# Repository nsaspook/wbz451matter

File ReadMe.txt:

Folder & File List:
Altium CAD\WBZ451 Curiosity Board-R7.zip: Contains the Altium Design Source Files for WBZ451 Curiosity Board
BOM\02-00307-R7_BOM.xls: Contains the Bill Of Materials for WBZ451 Curiosity Board
Gerber\05-00307-R4_PNP: Contains the pick and place files for WBZ451 Curiosity Board
Gerber\05-11423-R4: Contains the release gerber files for WBZ451 Curiosity Board
Gerber\04-11423-R4-D.pdf: Contains the Fab drawing for WBZ451 Curiosity Board
Gerber\04-11423-R4-PCB.pdf: Contains the PCB layer drawing for WBZ451 Curiosity Board
Gerber\05-00307-R4.pdf: Contains the Assembly drawings and 3D images for WBZ451 Curiosity Board
Schematics\03-00307-R7.pdf: Contains the Schematic drawing for WBZ451 Curiosity Board

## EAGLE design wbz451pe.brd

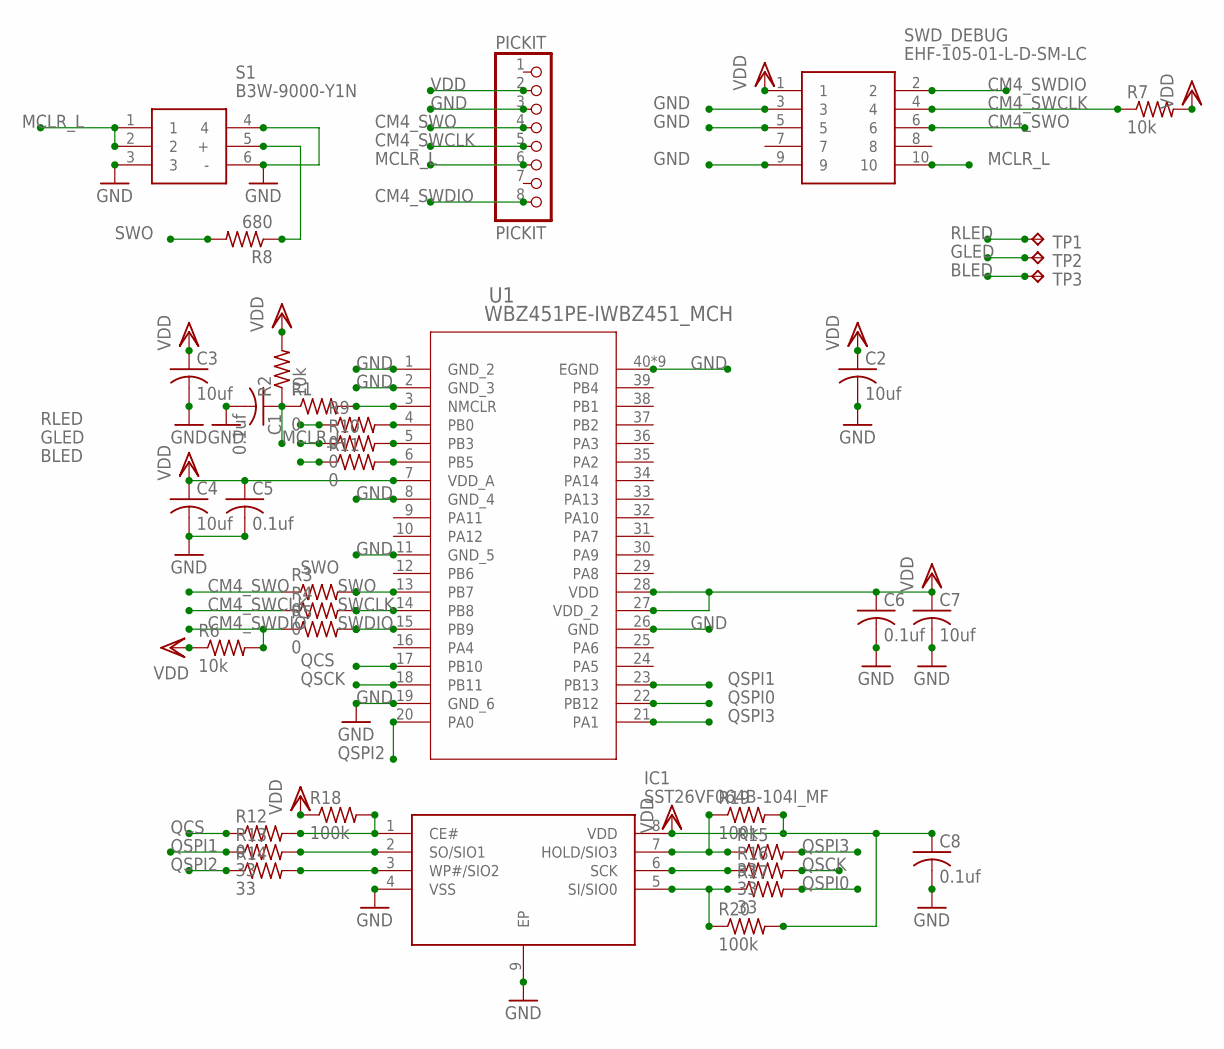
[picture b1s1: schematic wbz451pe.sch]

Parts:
C1, C5, C6, C8: 0.1uf; C0805
C2, C3, C4, C7: 10uf; C0805
IC1: SST26VF064B-104I_MF; SON127P600X500X80-9N
PICKIT: PICKIT; 1X08
R1, R3, R4, R5, R9, R10, R11: 0; M0805
R2, R6, R7: 10k; M0805
R8: 680; M0805
R12: 0; R0603
R13, R14, R15, R16, R17: 33; R0603
R18, R19, R20: 100k; R0603
S1: B3W-9000-Y1N; B3W-9_1-LED
SWD_DEBUG: EHF-105-01-L-D-SM-LC; EHF-105-01-XX-D-SM-LC
TP1, TP2, TP3: TPPAD1-13; P1-13
U1: WBZ451PE-IWBZ451_MCH; WBZ451_MCH

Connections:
BLED: R11.1, TP3.TP
CM4_SWCLK: PICKIT.5, R4.1, R7.1, SWD_DEBUG.4
CM4_SWDIO: PICKIT.8, R5.1, R6.2, SWD_DEBUG.2
CM4_SWO: PICKIT.4, R3.1, SWD_DEBUG.6
GLED: R10.1, TP2.TP
GND: C1.2, C2.2, C3.2, C4.2, C5.2, C6.2, C7.2, C8.2, IC1.4 (VSS), IC1.9 (EP), PICKIT.3, S1.3, S1.4, S1.6 (-), SWD_DEBUG.3, SWD_DEBUG.5, SWD_DEBUG.9, U1.1 (GND_2), U1.2 (GND_3), U1.8 (GND_4), U1.11 (GND_5), U1.19 (GND_6), U1.26 (GND), U1.40 (EGND), U1.41 (EGND), U1.42 (EGND), U1.43 (EGND), U1.44 (EGND), U1.45 (EGND), U1.46 (EGND), U1.47 (EGND), U1.48 (EGND)
MCLR_L: C1.1, PICKIT.6, R1.1, R2.1, S1.1, S1.2, SWD_DEBUG.10
unnamed: R1.2, U1.3 (NMCLR)
unnamed: R9.2, U1.4 (PB0)
unnamed: R8.1, S1.5 (+)
unnamed: R10.2, U1.5 (PB3)
unnamed: R11.2, U1.6 (PB5)
unnamed: IC1.1 (CE#), R12.2, R18.2
unnamed: IC1.2 (SO/SIO1), R13.2
unnamed: IC1.3 (WP#/SIO2), R14.2
unnamed: IC1.7 (HOLD/SIO3), R15.1, R19.1
unnamed: IC1.6 (SCK), R16.1
unnamed: IC1.5 (SI/SIO0), R17.1, R20.1
QCS: R12.1, U1.17 (PB10)
QSCK: R16.2, U1.18 (PB11)
QSPI0: R17.2, U1.22 (PB12)
QSPI1: R13.1, U1.23 (PB13)
QSPI2: R14.1, U1.20 (PA0)
QSPI3: R15.2, U1.21 (PA1)
RLED: R9.1, TP1.TP
SWCLK: R4.2, U1.14 (PB8)
SWDIO: R5.2, U1.15 (PB9)
SWO: R3.2, R8.2, U1.13 (PB7)
VDD: C2.1, C3.1, C4.1, C5.1, C6.1, C7.1, C8.1, IC1.8 (VDD), PICKIT.2, R2.2, R6.1, R7.2, R18.1, R19.2, R20.2, SWD_DEBUG.1, U1.7 (VDD_A), U1.27 (VDD_2), U1.28 (VDD)

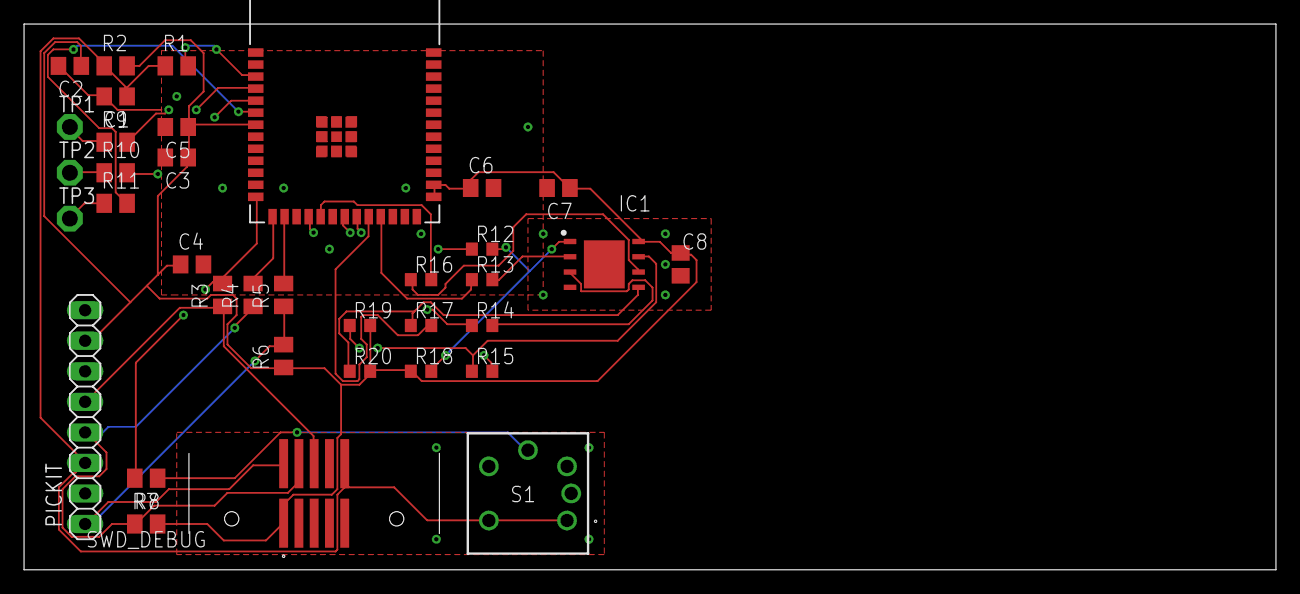
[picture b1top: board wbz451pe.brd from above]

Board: 4 copper layers, 104.1 x 45.4 mm, 36 parts (0 on the bottom side), 29 nets.

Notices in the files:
parts and their libraries:
COPYRIGHT: Copyright (C) 2024 Ultra Librarian. All rights reserved.
